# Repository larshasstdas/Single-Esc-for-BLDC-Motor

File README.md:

# Single ESC for BLDC Motor

A custom single-channel ESC (Electronic Speed Controller) for BLDC motors. I want to programm and test the esc before modifying it into a 4in1 esc i can use for flying a drone.

## Overview

This repository contains the KiCad schematic and PCB layout for a single-channel ESC. The design is based on the DRV8353 gate driver and BSC010N04LSI MOSFETs, controlled by an STM32G431 microcontroller. It includes a buck converter for onboard power regulation, MOSFET-based battery backflow protection, and BEMF sensing for sensorless motor control.

## Files
```
├── KiCad_Files/              # KiCad design source
│   ├── SingleEsc.kicad_pro   # KiCad project file
│   ├── SingleEsc.kicad_sch   # Schematic
│   ├── SingleEsc.kicad_pcb   # PCB layout
│   ├── SingleEsc-job.gbrjob  # Gerber job file
│   ├── SingleEsc-all-pos.csv # Component placement export
│   ├── footprints/           # Custom footprint library
│   ├── myBibs/               # Custom schematic symbol library
│   └── fp-lib-table          # Footprint library table
│
├── Gerber&BOM/               # Manufacturing data
│   ├── GerberESC/            # Gerber and drill files
│   ├── DigiKey_ESC_BOM.csv   # Bill of materials (CSV)
│   ├── DigiKey_ESC_BOM.xlsx  # Bill of materials (Excel)
│   ├── ESC_PickAndPlace.csv  # Pick & place (CSV)
│   └── ESC_PickAndPlace.xlsx # Pick & place (Excel)
│
├── Gerber&BOM.zip            # Zipped Gerber, BOM and Pick & Place files
└── README.md
```
## Bill of Materials

A BOM with all components for buying on Digikey is available in the project files. Some parts need to be bought elsewhere for example the XT60 connector.

## AI Usage

AI was used for helping with a basic idea for a layout, learning about components and an idea of where to buy parts.

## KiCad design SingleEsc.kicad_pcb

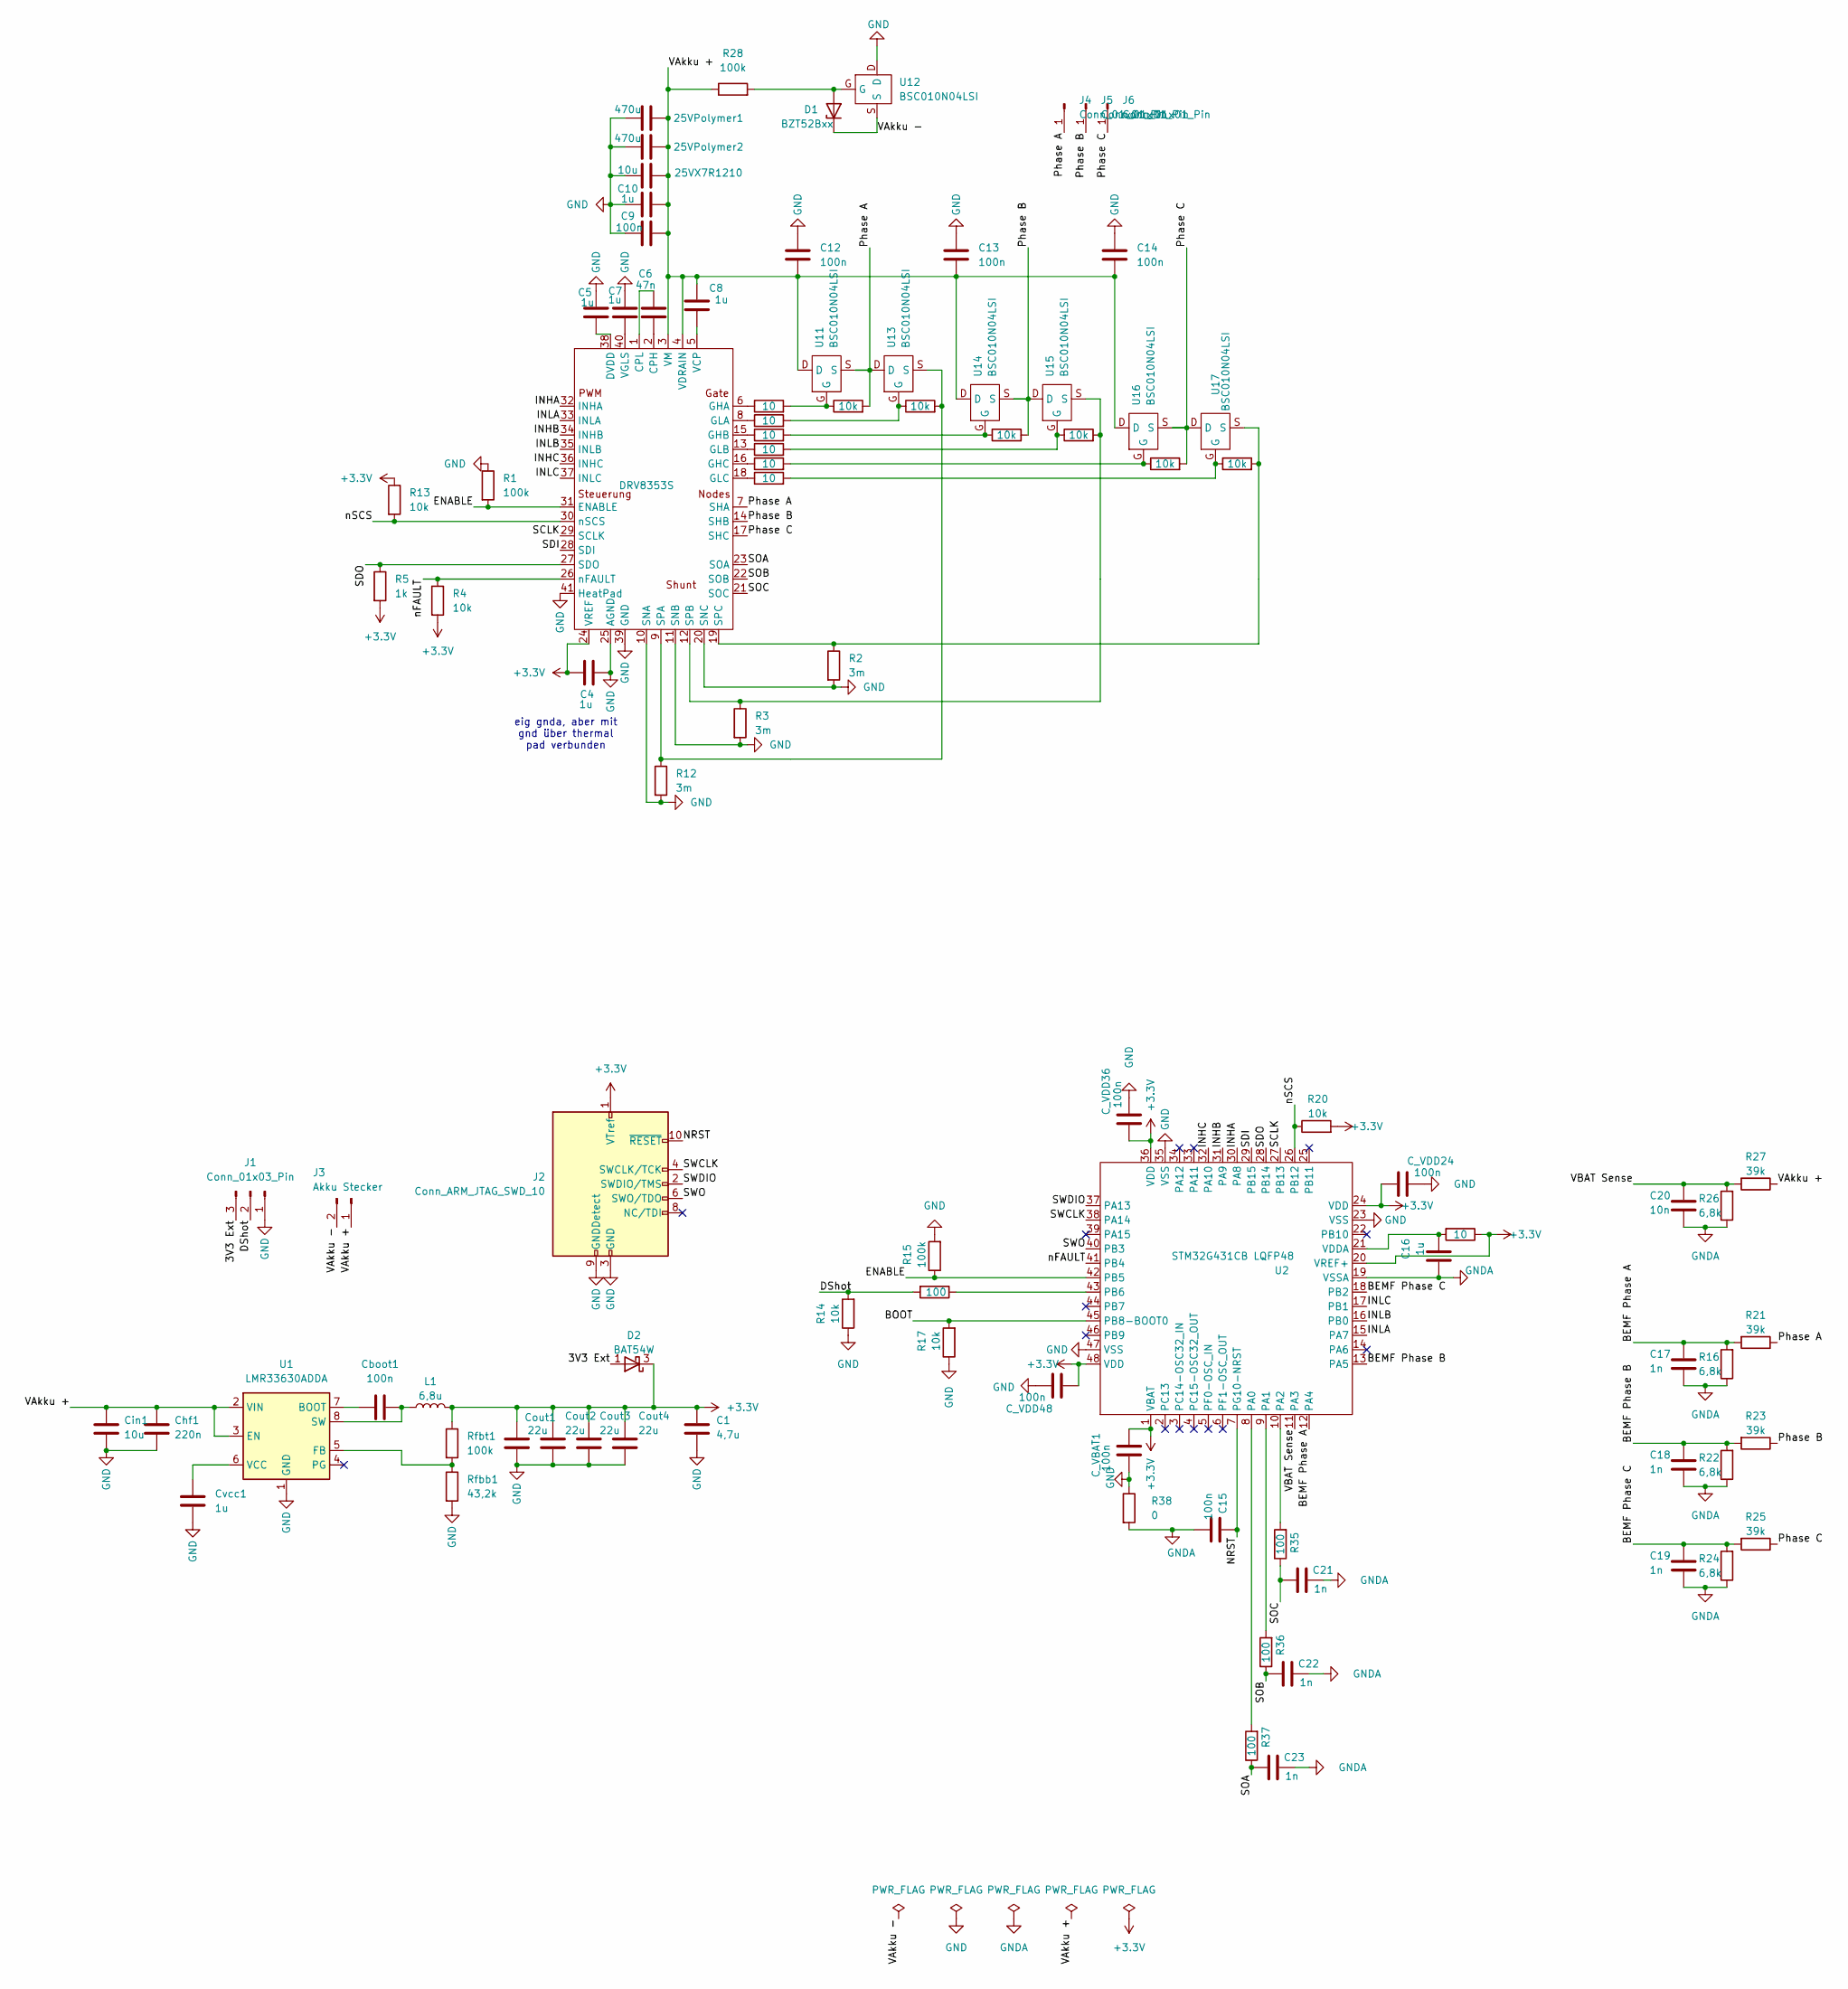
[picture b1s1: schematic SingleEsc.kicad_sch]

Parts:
25VPolymer1, 25VPolymer2: 470u; C_1206_3216Metric
25VX7R1210: 10u; C_0603_1608Metric
C1: 4,7u; C_0603_1608Metric
C4, C5, C7, C8, C10, C16: 1u; C_0603_1608Metric
C6: 47n; C_0603_1608Metric
C9, C15: 100n; C_0603_1608Metric
C12, C13, C14: 100n; C_0805_2012Metric
C17, C18, C19, C21, C22, C23: 1n; C_0603_1608Metric
C20: 10n; C_0603_1608Metric
C_VBAT1: 100n; C_0603_1608Metric
C_VDD24, C_VDD36, C_VDD48: 100n; C_0603_1608Metric
Cboot1: 100n; C_0603_1608Metric
Chf1: 220n; C_0603_1608Metric
Cin1: 10u; C_1210_3225Metric
Cout1, Cout2, Cout3, Cout4: 22u; C_1210_3225Metric
Cvcc1: 1u; C_0603_1608Metric
D1: BZT52Bxx; D_SOD-123F
D2: BAT54W; SOT-323_SC-70
J1: Conn_01x03_Pin; PinHeader_1x03_P2.54mm_Horizontal
J2: Conn_ARM_JTAG_SWD_10; PinHeader_2x05_P1.27mm_Vertical_SMD
J3: Akku Stecker; AMASS_XT60PW-M_1x02_P7.20mm_Horizontal
J4, J5, J6: Conn_01x01_Pin; SolderWirePad_1x01_SMD_5x10mm
L1: 6,8u; L_Wurth_WE-LHMI-7030
R1: 100k; C_0603_1608Metric
R2, R3, R12: 3m; R_2512_6332Metric
R4, R13: 10k; C_0603_1608Metric
R5: 1k; C_0603_1608Metric
R6, R7, R8, R9, R10, R11, R18: 10; R_0805_2012Metric
R14, R17, R20, R29, R30, R31, R32, R33, R34: 10k; R_0603_1608Metric
R15, R28: 100k; R_0603_1608Metric
R16, R22, R24, R26: 6,8k; R_0603_1608Metric
R19, R35, R36, R37: 100; R_0603_1608Metric
R21, R23, R25, R27: 39k; R_0603_1608Metric
R38: 0; R_0603_1608Metric
Rfbb1: 43,2k; C_0603_1608Metric
Rfbt1: 100k; C_0603_1608Metric
U1: LMR33630ADDA; Texas_HSOP-8-1EP_3.9x4.9mm_P1.27mm_ThermalVias
U2: STM32G431CB LQFP48
U11, U12, U13, U14, U15, U16, U17: BSC010N04LSI
U18: DRV8353S

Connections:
+3.3V: C1.1, C4.1, C_VBAT1.1, C_VDD24.1, C_VDD36.1, C_VDD48.1, Cout1.1, Cout2.1, Cout3.1, Cout4.1, D2.3 (K), J2.1 (VTref), L1.1, R4.2, R5.2, R13.1, R18.1, R20.2, Rfbt1.1, U2.1 (VBAT), U2.20 (VREF+), U2.24 (VDD), U2.36 (VDD), U2.48 (VDD), U18.24 (VREF)
/3V3 Ext: D2.1 (A), J1.3
/BEMF Phase A: C17.1, R16.2, R21.2, U2.12 (PA4)
/BEMF Phase B: C18.1, R22.2, R23.2, U2.13 (PA5)
/BEMF Phase C: C19.1, R24.2, R25.2, U2.18 (PB2)
/BOOT: R17.2, U2.45 (PB8-BOOT0)
/DShot: J1.2, R14.2, R19.2
/ENABLE: R1.2, R15.1, U2.42 (PB5), U18.31 (ENABLE)
/INHA: U2.30 (PA8), U18.32 (INHA)
/INHB: U2.31 (PA9), U18.34 (INHB)
/INHC: U2.32 (PA10), U18.36 (INHC)
/INLA: U2.15 (PA7), U18.33 (INLA)
/INLB: U2.16 (PB0), U18.35 (INLB)
/INLC: U2.17 (PB1), U18.37 (INLC)
/NRST: C15.1, J2.10 (~RESET), U2.7 (PG10-NRST)
/Phase A: J4.1 (Pin_1_1), R21.1, R29.2, U11.S, U13.D, U18.7 (SHA)
/Phase B: J5.1 (Pin_1_1), R23.1, R31.2, U14.S, U15.D, U18.14 (SHB)
/Phase C: J6.1 (Pin_1_1), R25.1, R33.2, U16.S, U17.D, U18.17 (SHC)
/SCLK: U2.27 (PB13), U18.29 (SCLK)
/SDI: U2.29 (PB15), U18.28 (SDI)
/SDO: R5.1, U2.28 (PB14), U18.27 (SDO)
/SOA: C23.2, R37.1, U18.23 (SOA)
/SOB: C22.2, R36.1, U18.22 (SOB)
/SOC: C21.2, R35.1, U18.21 (SOC)
/SWCLK: J2.4 (SWCLK/TCK), U2.38 (PA14)
/SWDIO: J2.2 (SWDIO/TMS), U2.37 (PA13)
/SWO: J2.6 (SWO/TDO), U2.40 (PB3)
/VAkku +: 25VPolymer1.2, 25VPolymer2.2, 25VX7R1210.2, C8.1, C9.2, C10.2, C12.1, C13.1, C14.1, Chf1.1, Cin1.1, J3.1, R27.1, R28.1, U1.2 (VIN), U1.3 (EN), U11.D, U14.D, U16.D, U18.3 (VM), U18.4 (VDRAIN)
/VAkku -: D1.1 (K), J3.2, U12.S
/VBAT Sense: C20.1, R26.2, R27.2, U2.11 (PA3)
/nFAULT: R4.1, U2.41 (PB4), U18.26 (nFAULT)
/nSCS: R13.2, R20.1, U2.26 (PB12), U18.30 (nSCS)
GND: 25VPolymer1.1, 25VPolymer2.1, 25VX7R1210.1, C1.2, C4.2, C5.1, C7.1, C9.1, C10.1, C12.2, C13.2, C14.2, C_VBAT1.2, C_VDD24.2, C_VDD36.2, C_VDD48.2, Chf1.2, Cin1.2, Cout1.2, Cout2.2, Cout3.2, Cout4.2, Cvcc1.2, J1.1, J2.3 (GND), J2.5 (GND), J2.9 (GNDDetect), R1.1, R2.2, R3.2, R12.2, R14.1, R15.2, R17.1, R38.1, Rfbb1.2, U1.1 (GND), U1.9 (GND), U2.23 (VSS), U2.35 (VSS), U2.47 (VSS), U12.D, U18.10 (SNA), U18.11 (SNB), U18.20 (SNC), U18.25 (AGND), U18.39 (GND), U18.41 (HeatPad)
GNDA: C15.2, C16.1, C17.2, C18.2, C19.2, C20.2, C21.1, C22.1, C23.1, R16.1, R22.1, R24.1, R26.1, R38.2, U2.19 (VSSA)
unnamed: D1.2 (A), R28.2, U12.G
unnamed: R10.2, R33.1, U16.G
unnamed: R11.2, R34.1, U17.G
unnamed: R6.2, R29.1, U11.G
unnamed: R7.2, R30.1, U13.G
unnamed: R8.2, R31.1, U14.G
unnamed: R9.2, R32.1, U15.G
unnamed: Cboot1.1, U1.7 (BOOT)
unnamed: Rfbb1.1, Rfbt1.2, U1.5 (FB)
unnamed: Cboot1.2, L1.2, U1.8 (SW)
unnamed: Cvcc1.1, U1.6 (VCC)
unnamed: R37.2, U2.8 (PA0)
unnamed: R36.2, U2.9 (PA1)
unnamed: R35.2, U2.10 (PA2)
unnamed: R19.1, U2.43 (PB6)
unnamed: C16.2, R18.2, U2.21 (VDDA)
unnamed: C6.2, U18.2 (CPH)
unnamed: C6.1, U18.1 (CPL)
unnamed: C5.2, U18.38 (DVDD)
unnamed: R6.1, U18.6 (GHA)
unnamed: R8.1, U18.15 (GHB)
unnamed: R10.1, U18.16 (GHC)
unnamed: R7.1, U18.8 (GLA)
unnamed: R9.1, U18.13 (GLB)
unnamed: R11.1, U18.18 (GLC)
unnamed: R12.1, R30.2, U13.S, U18.9 (SPA)
unnamed: R3.1, R32.2, U15.S, U18.12 (SPB)
unnamed: R2.1, R34.2, U17.S, U18.19 (SPC)
unnamed: C8.2, U18.5 (VCP)
unnamed: C7.2, U18.40 (VGLS)

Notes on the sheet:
eig gnda, aber mit gnd über thermal pad verbunden

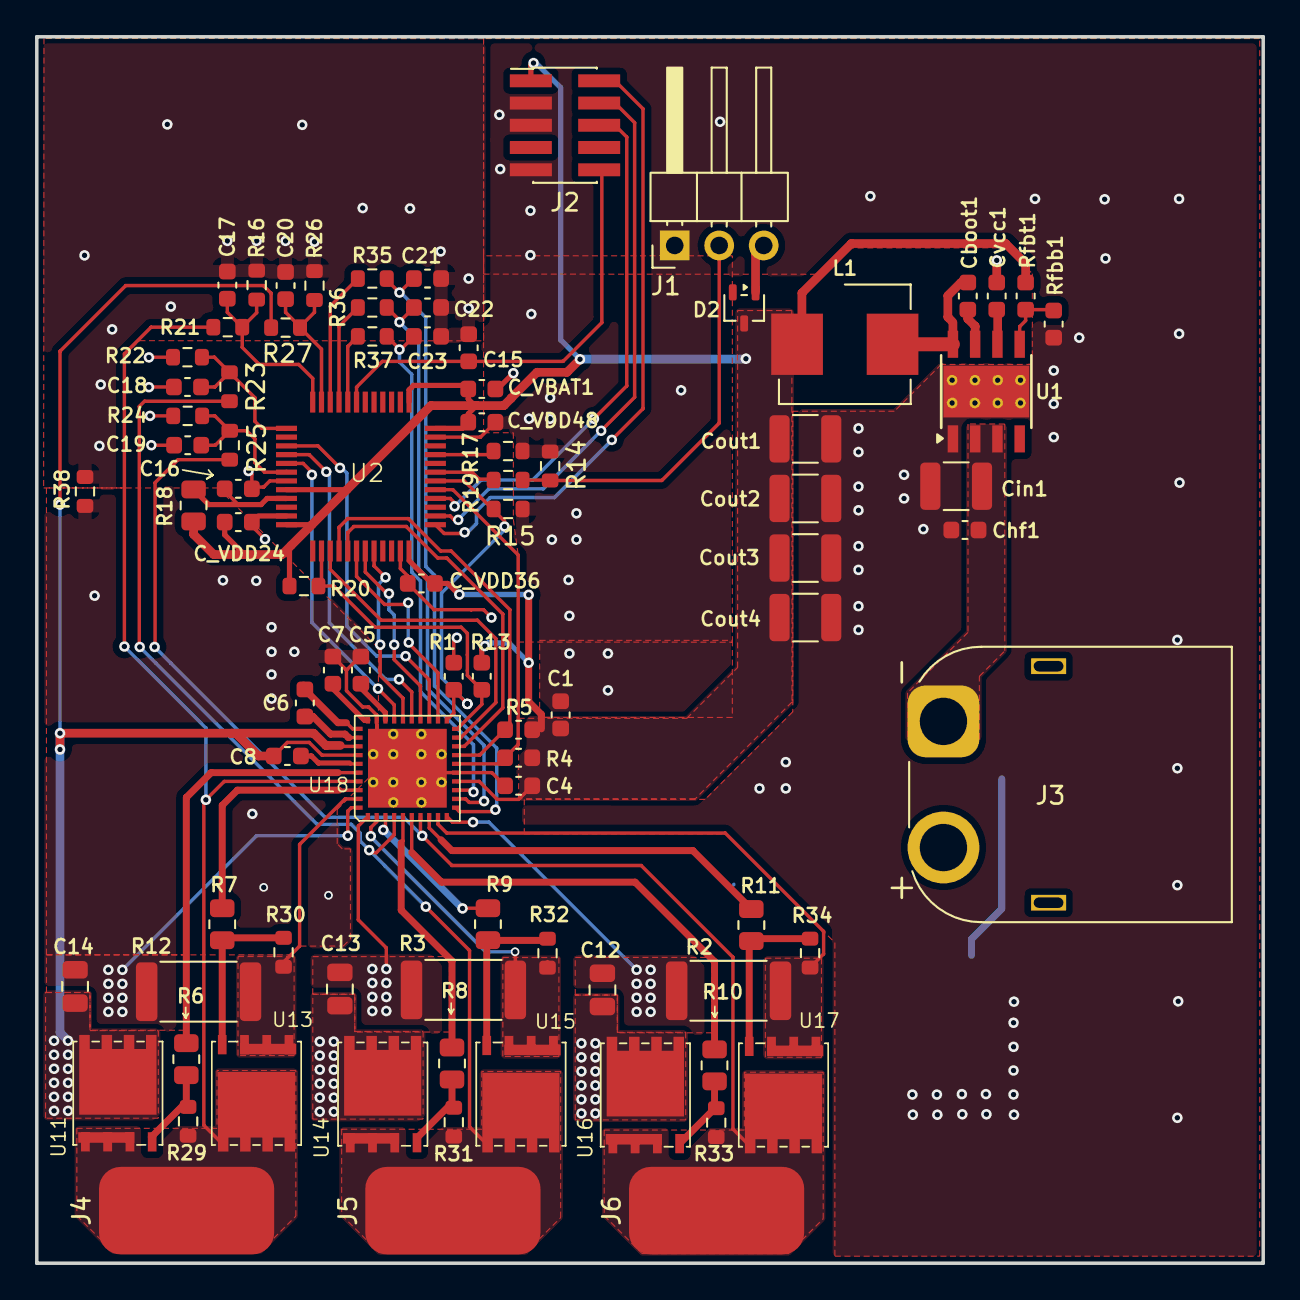
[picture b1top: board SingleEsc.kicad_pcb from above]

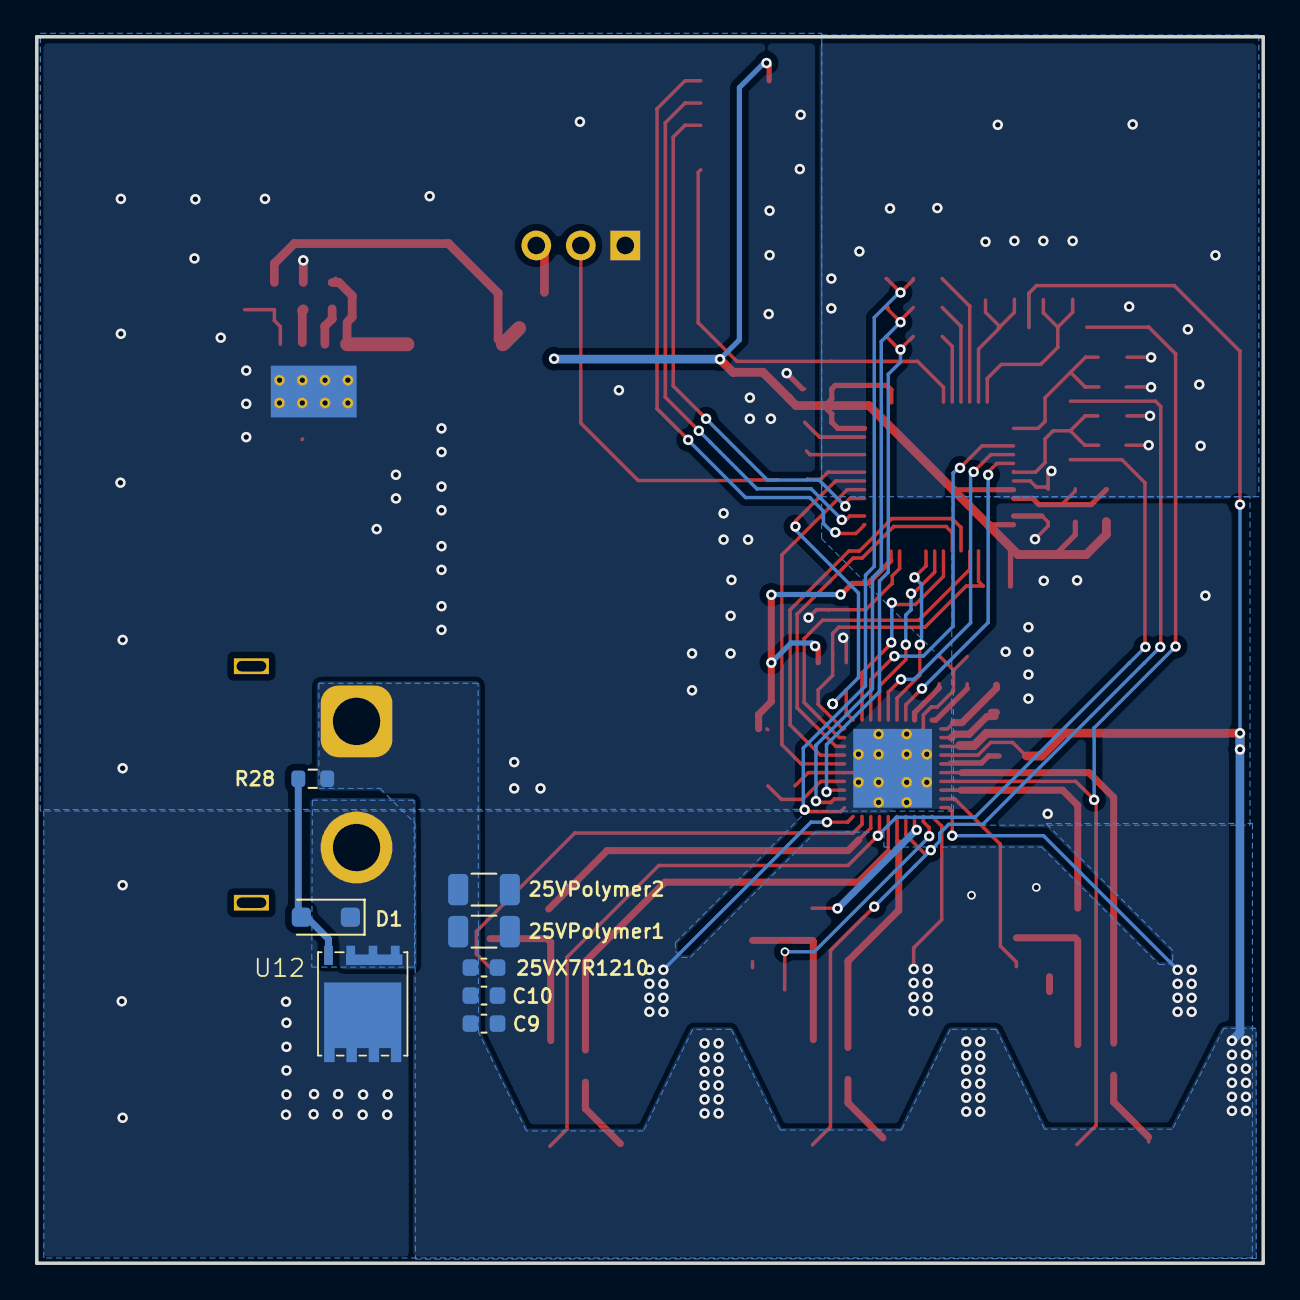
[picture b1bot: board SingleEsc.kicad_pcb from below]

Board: 2 copper layers, 70.0 x 70.0 mm, 94 parts (8 on the bottom side), 64 nets.

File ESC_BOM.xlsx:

Pos. | Kategorie | Referenz | Wert | Spannung | Gehäuse / Footprint | Hersteller-Teilenr. | Anzahl | Bemerkung
Halbleiter (Aktive Bauteile)
1 | Halbleiter | U2 | STM32G431CBT6 | - | LQFP-48 (7×7 mm) | STM32G431CBT6 | 1 | Hauptmikrocontroller
2 | Halbleiter | U18 | DRV8353S | - | WQFN-40 (6×6 mm, EP) | DRV8353SRTAR | 1 | Gate-Treiber, mit SPI
3 | Halbleiter | U1 | LMR33630ADDA | - | HSOIC-8 PowerPad | LMR33630ADDAR | 1 | 3,3-V Buck-Konverter, 400 kHz
4 | Halbleiter | U11–U17 | BSC010N04LSI | 40 V | TDSON-8 | BSC010N04LSIATMA1 | 6 | Power-MOSFETs Half-Bridge (3× HS, 3× LS)
5 | Halbleiter | U12 | BSC010N04LSI | 40 V | TDSON-8 | BSC010N04LSIATMA1 | 1 | Verpolschutz-FET
6 | Halbleiter | D1 | BZT52C15 | 15 V | SOD-123 | BZT52C15-7-F | 1 | Zenerdiode (Verpolschutz Gate-Schutz)
7 | Halbleiter | D2 | BAT54W | 30 V | SOD-123 | BAT54W-7-F | 1 | Schottky-Diode (3,3-V-Backfeed-Schutz)
Induktivität
8 | Induktivität | L1 | 6,8 µH | - | SMD 5×5 oder 6×6 mm | Würth 74437346068 | 1 | I_sat ≥ 4,5 A, geschirmt, für Buck-Konverter
Strom-Mess-Shunts
9 | Shunt | R2, R3, R12 | 3 mΩ | - | 2512 (3-W-Klasse) | CSS2H-2512K-L1L00FE | 3 | Strommessung, Bourns oder Vishay WSL2512R0030FEA
Widerstände 0603 (1%, X7R-Klasse)
10 | Widerstand | R1 | 100 kΩ | - | 0603 | RC0603FR-07100KL | 1 | DRV ENABLE-Pulldown
11 | Widerstand | R4 | 10 kΩ | - | 0603 | RC0603FR-0710KL | 1 | nFAULT Pull-Up
12 | Widerstand | R5 | 1 kΩ | - | 0603 | RC0603FR-071KL | 1 | SDO-Widerstand
13 | Widerstand | R13 | 10 kΩ | - | 0603 | RC0603FR-0710KL | 1 | ENABLE-Serienwiderstand
14 | Widerstand | R14 | 10 kΩ | - | 0603 | RC0603FR-0710KL | 1 | DShot-Pulldown
15 | Widerstand | R15 | 100 kΩ | - | 0603 | RC0603FR-07100KL | 1 | ENABLE-Pulldown am MCU
16 | Widerstand | R17 | 10 kΩ | - | 0603 | RC0603FR-0710KL | 1 | BOOT-Pulldown
17 | Widerstand | R20 | 10 kΩ | - | 0603 | RC0603FR-0710KL | 1 | nSCS Pull-Up
18 | Widerstand | R28 | 100 kΩ | - | 0603 | RC0603FR-07100KL | 1 | Verpolschutz Gate-Pullup
19 | Widerstand | R_GS_HA-LC | 10 kΩ | - | 0603 | RC0603FR-0710KL | 6 | Gate-Source-Pulldowns an FETs (1× pro FET)
20 | Widerstand | R_F_A-C | 100 Ω | - | 0603 | RC0603FR-07100RL | 3 | DRV-Strom-Filter (R35, R36, R37)
21 | Widerstand | R_Gate | 10 Ω | - | 0603 | RC0603FR-0710RL | 6 | Gate-Widerstände an FETs (zwischen DRV und Gate)
22 | Widerstand | R_DShot | 100 Ω | - | 0603 | RC0603FR-07100RL | 1 | DShot-Schutzwiderstand
23 | Widerstand | R_VDDA | 10 Ω | - | 0603 | RC0603FR-0710RL | 1 | VDDA-Filter (LC zu MCU-VDDA)
24 | Widerstand | R21, R23, R25, R27 | 39 kΩ | - | 0603 | RC0603FR-0739KL | 4 | BEMF/VBAT-Teiler R_top
25 | Widerstand | R16, R22, R24, R26 | 6,8 kΩ | - | 0603 | RC0603FR-076K8L | 4 | BEMF/VBAT-Teiler R_bot
26 | Widerstand | Rfbt | 100 kΩ | - | 0603 | RC0603FR-07100KL | 1 | Buck Feedback (LMR33630)
27 | Widerstand | Rfbb | 43,2 kΩ | - | 0603 | RC0603FR-0743K2L | 1 | Buck Feedback (LMR33630)
Kondensatoren - Keramik X7R
28 | Kondensator | C1 | 4,7 µF | 25 V | 0805 X7R | GRM21BR71E475KA73L | 1 | MCU-Bulk
29 | Kondensator | C4 | 1 µF | 16 V | 0603 X7R | GRM188R71C105KA12D | 1 | DRV-VREF (auf GNDA)
30 | Kondensator | C5, C7 | 1 µF | 25 V | 0603 X7R | GRM188R71E105KA12D | 2 | DRV-DVDD (C5), DRV-VGLS (C7)
31 | Kondensator | C6 | 47 nF | 25 V | 0603 X7R | GRM188R71E473KA01D | 1 | DRV-Charge-Pump CPL/CPH
32 | Kondensator | C8 | 1 µF | 25 V | 0603 X7R | GRM188R71E105KA12D | 1 | DRV-VCP
33 | Kondensator | C9 | 100 nF | 25 V | 0603 X7R | GRM188R71E104KA01D | 1 | VAkku-Bypass HF
34 | Kondensator | C10 | 1 µF | 25 V | 0603 X7R | GRM188R71E105KA12D | 1 | VAkku-Bypass mittel
35 | Kondensator | C11 (10µ) | 10 µF | 25 V | 1210 X7R | GRM32ER71E106KA12L | 1 | VAkku-Bypass mittel (Bulk-Stack)
36 | Kondensator | C12, C13, C14 | 100 nF | 25 V | 0603 X7R | GRM188R71E104KA01D | 3 | Half-Bridge-Bypass (1× pro Phase)
37 | Kondensator | C15 | 100 nF | 16 V | 0603 X7R | GRM188R71C104KA01D | 1 | NRST-Cap
38 | Kondensator | C16 | 1 µF | 16 V | 0603 X7R | GRM188R71C105KA12D | 1 | VDDA-Cap (auf GNDA)
39 | Kondensator | C17, C18, C19 | 1 nF | 16 V | 0603 X7R | GRM188R71C102KA01D | 3 | BEMF-Filter
40 | Kondensator | C20 | 10 nF | 16 V | 0603 X7R | GRM188R71C103KA01D | 1 | VBAT-Sense-Filter
41 | Kondensator | C21, C22, C23 | 1 nF | 16 V | 0603 X7R | GRM188R71C102KA01D | 3 | DRV-Strom-Filter
42 | Kondensator | CIN1 | 10 µF | 50 V | 1210 X7R | GRM32ER71H106KA12L | 1 | Buck-Eingang
43 | Kondensator | CHF | 220 nF | 50 V | 0603 X7R | GRM188R71H224KA93D | 1 | Buck-HF-Bypass am VIN
44 | Kondensator | CBOOT | 100 nF | 25 V | 0603 X7R | GRM188R71E104KA01D | 1 | Buck-Bootstrap
45 | Kondensator | CVCC | 1 µF | 16 V | 0603 X7R | GRM188R71C105KA12D | 1 | Buck-VCC
46 | Kondensator | COUT | 22 µF | 16 V | 1210 X7R | GRM32ER71C226KE15L | 4 | Buck-Ausgang
47 | Kondensator | C_VDD24, C_VDD36, C_VDD48, C_VBAT | 100 nF | 16 V | 0603 X7R | GRM188R71C104KA01D | 4 | MCU VDD/VBAT-Pin-Bypass
Aluminium-Polymer Bulk-Elkos
48 | Bulk-Elko | C2, C3 | 470 µF | 25-35 V | 10×10 mm radial SMD | EEH-ZA1V471P | 2 | Polymer Low-ESR, Panasonic / Würth 875115342009
Stecker
49 | Stecker | J1 | PinHeader 3-pin 2,54 mm | - | 1×3, 2,54 mm Pitch | 61300311121 | 1 | DShot/FC-Anschluss (Würth oder generisch)
50 | Stecker | J2 | Cortex SWD 10-Pin | - | 2×5, 1,27 mm Pitch | FTSH-105-01-L-DV | 1 | SWD-Programmieranschluss (Samtec o. ähnlich)
51 | Stecker | J3 | XT60 | - | XT60 PCB-Mount | XT60E-M | 1 | Akku-Stecker (z. B. Amass XT60E-M)
ZUSAMMENFASSUNG
 |  |  |  |  |  | Bauteile gesamt: | 90

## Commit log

2026-06-06 Single Esc Pcb Layout
2026-06-06 added BOM
2026-06-06 commit vor pull
2026-06-06 commit readme
2026-06-06 renamed BOM
2026-06-13 updated BOM
2026-06-23 sorted repo and added PichAndPlace
